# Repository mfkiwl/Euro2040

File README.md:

# Euro2040
 
### An RP2040 based development board designed for use in Eurorack modules

The key aims of this project are to create a board which can be used to create a Eurorack module (or standalone synthesiser) with no need for extra buffering or active circuitry.  
The board will contain internal buffering, amplification, and protection, to allow the GPIO pins to be used with up to 12V signals, allowing users to connect the pins directly to jacks to interface with other Eurorack compliant modules.

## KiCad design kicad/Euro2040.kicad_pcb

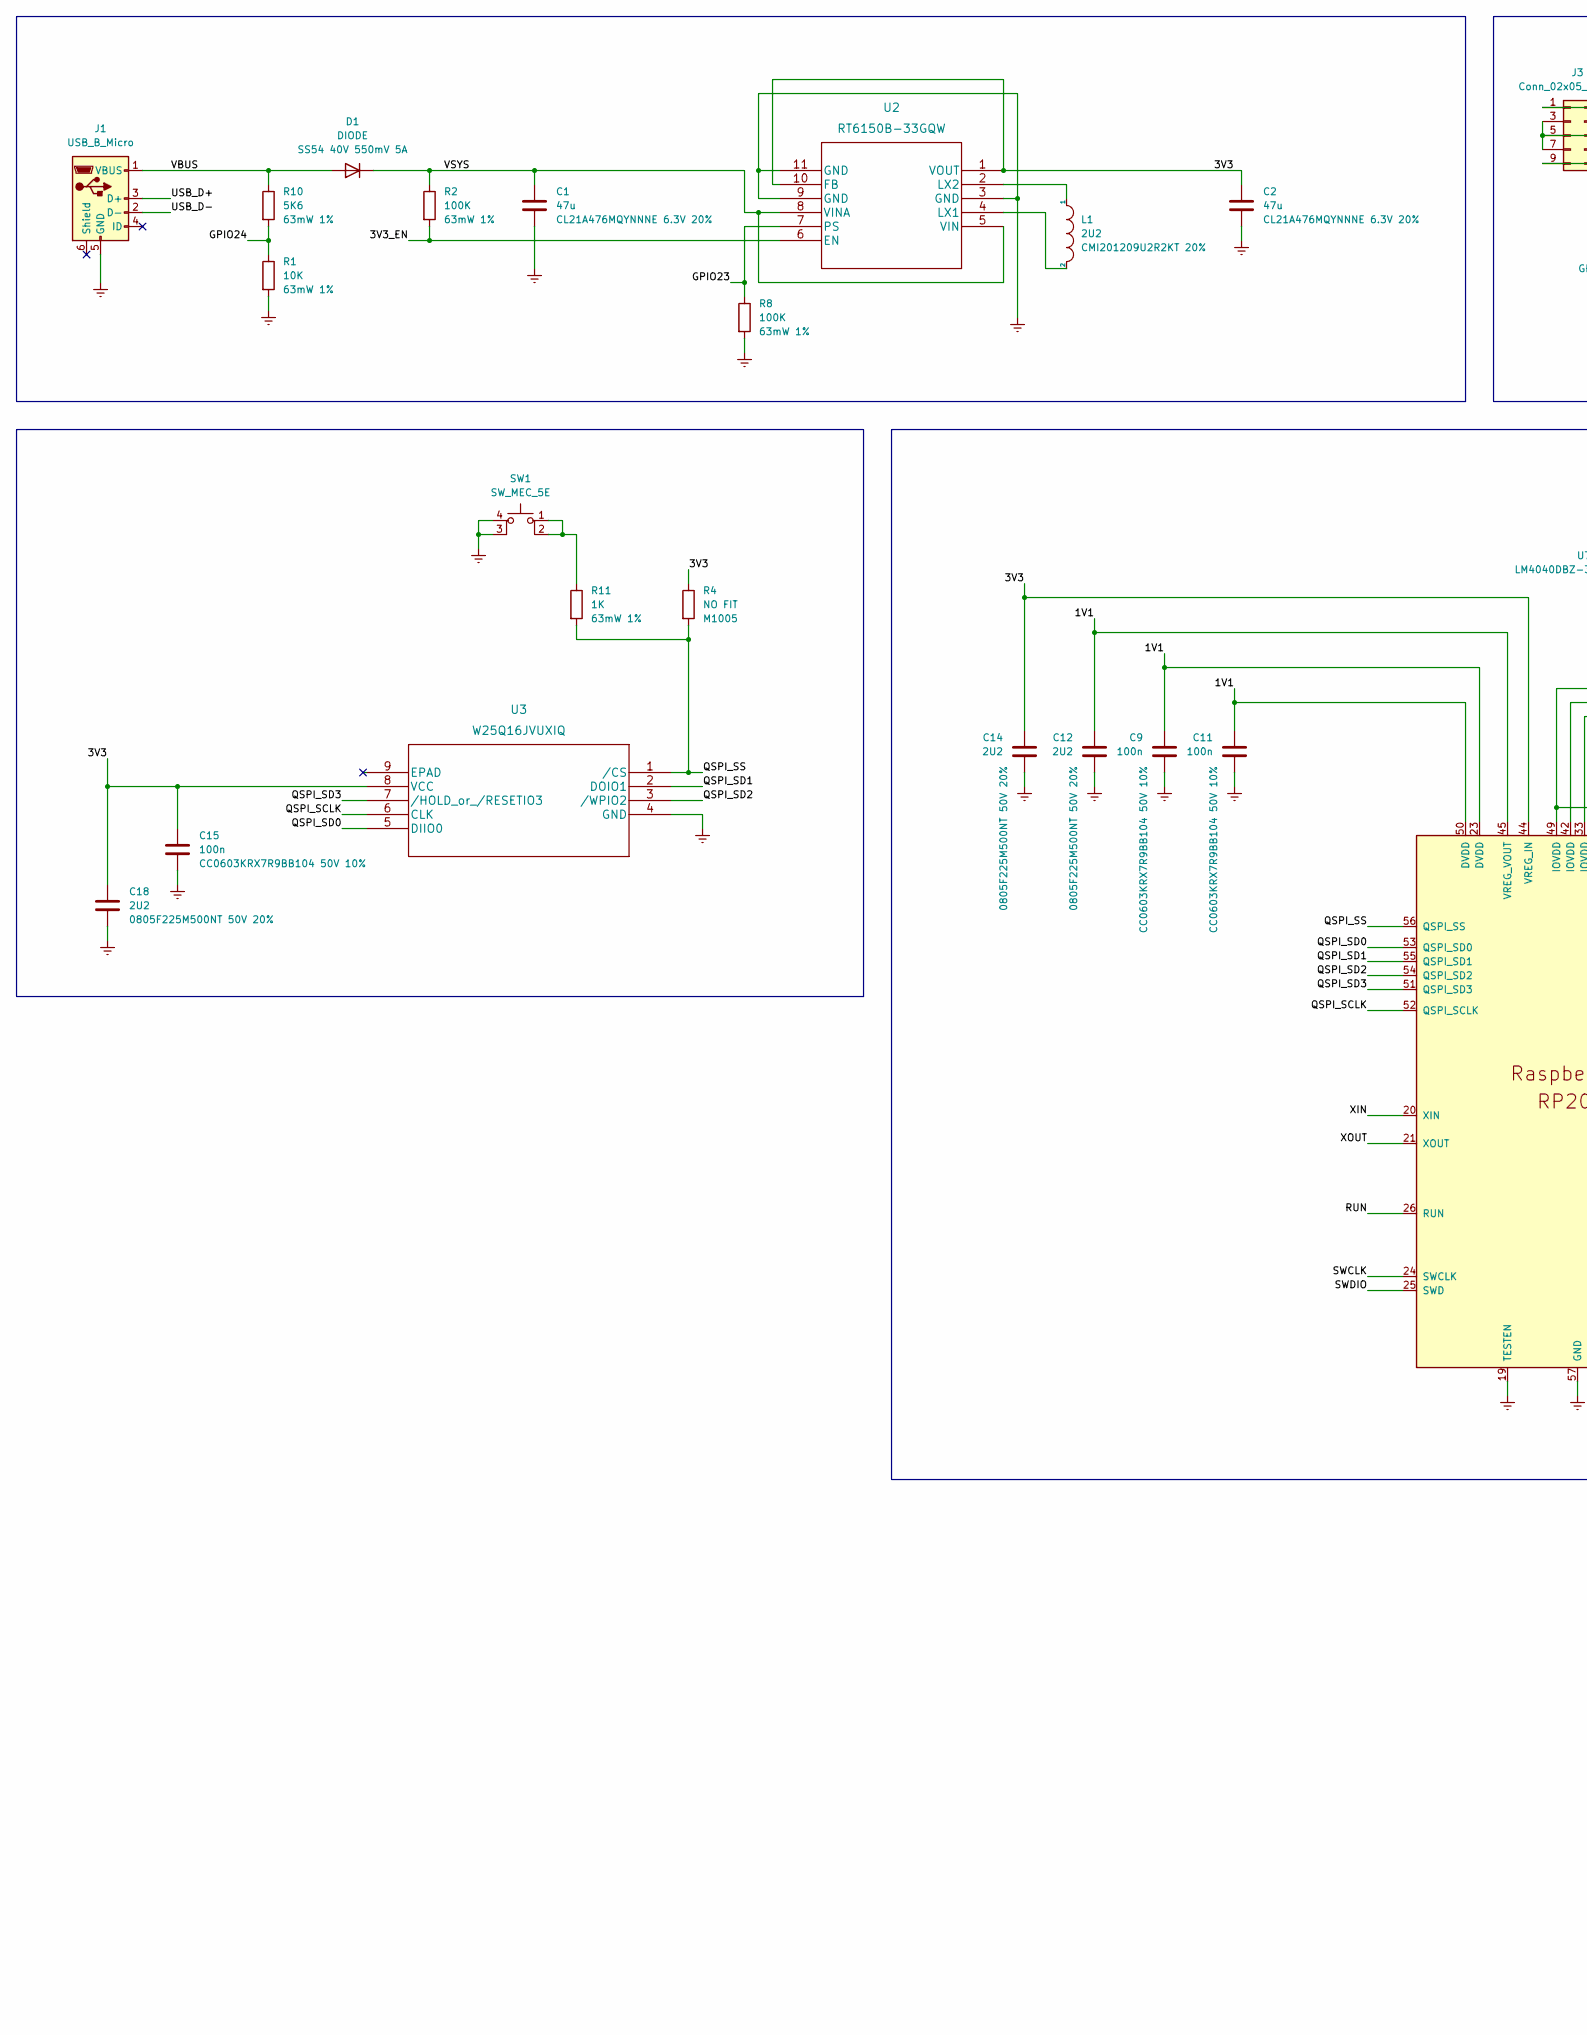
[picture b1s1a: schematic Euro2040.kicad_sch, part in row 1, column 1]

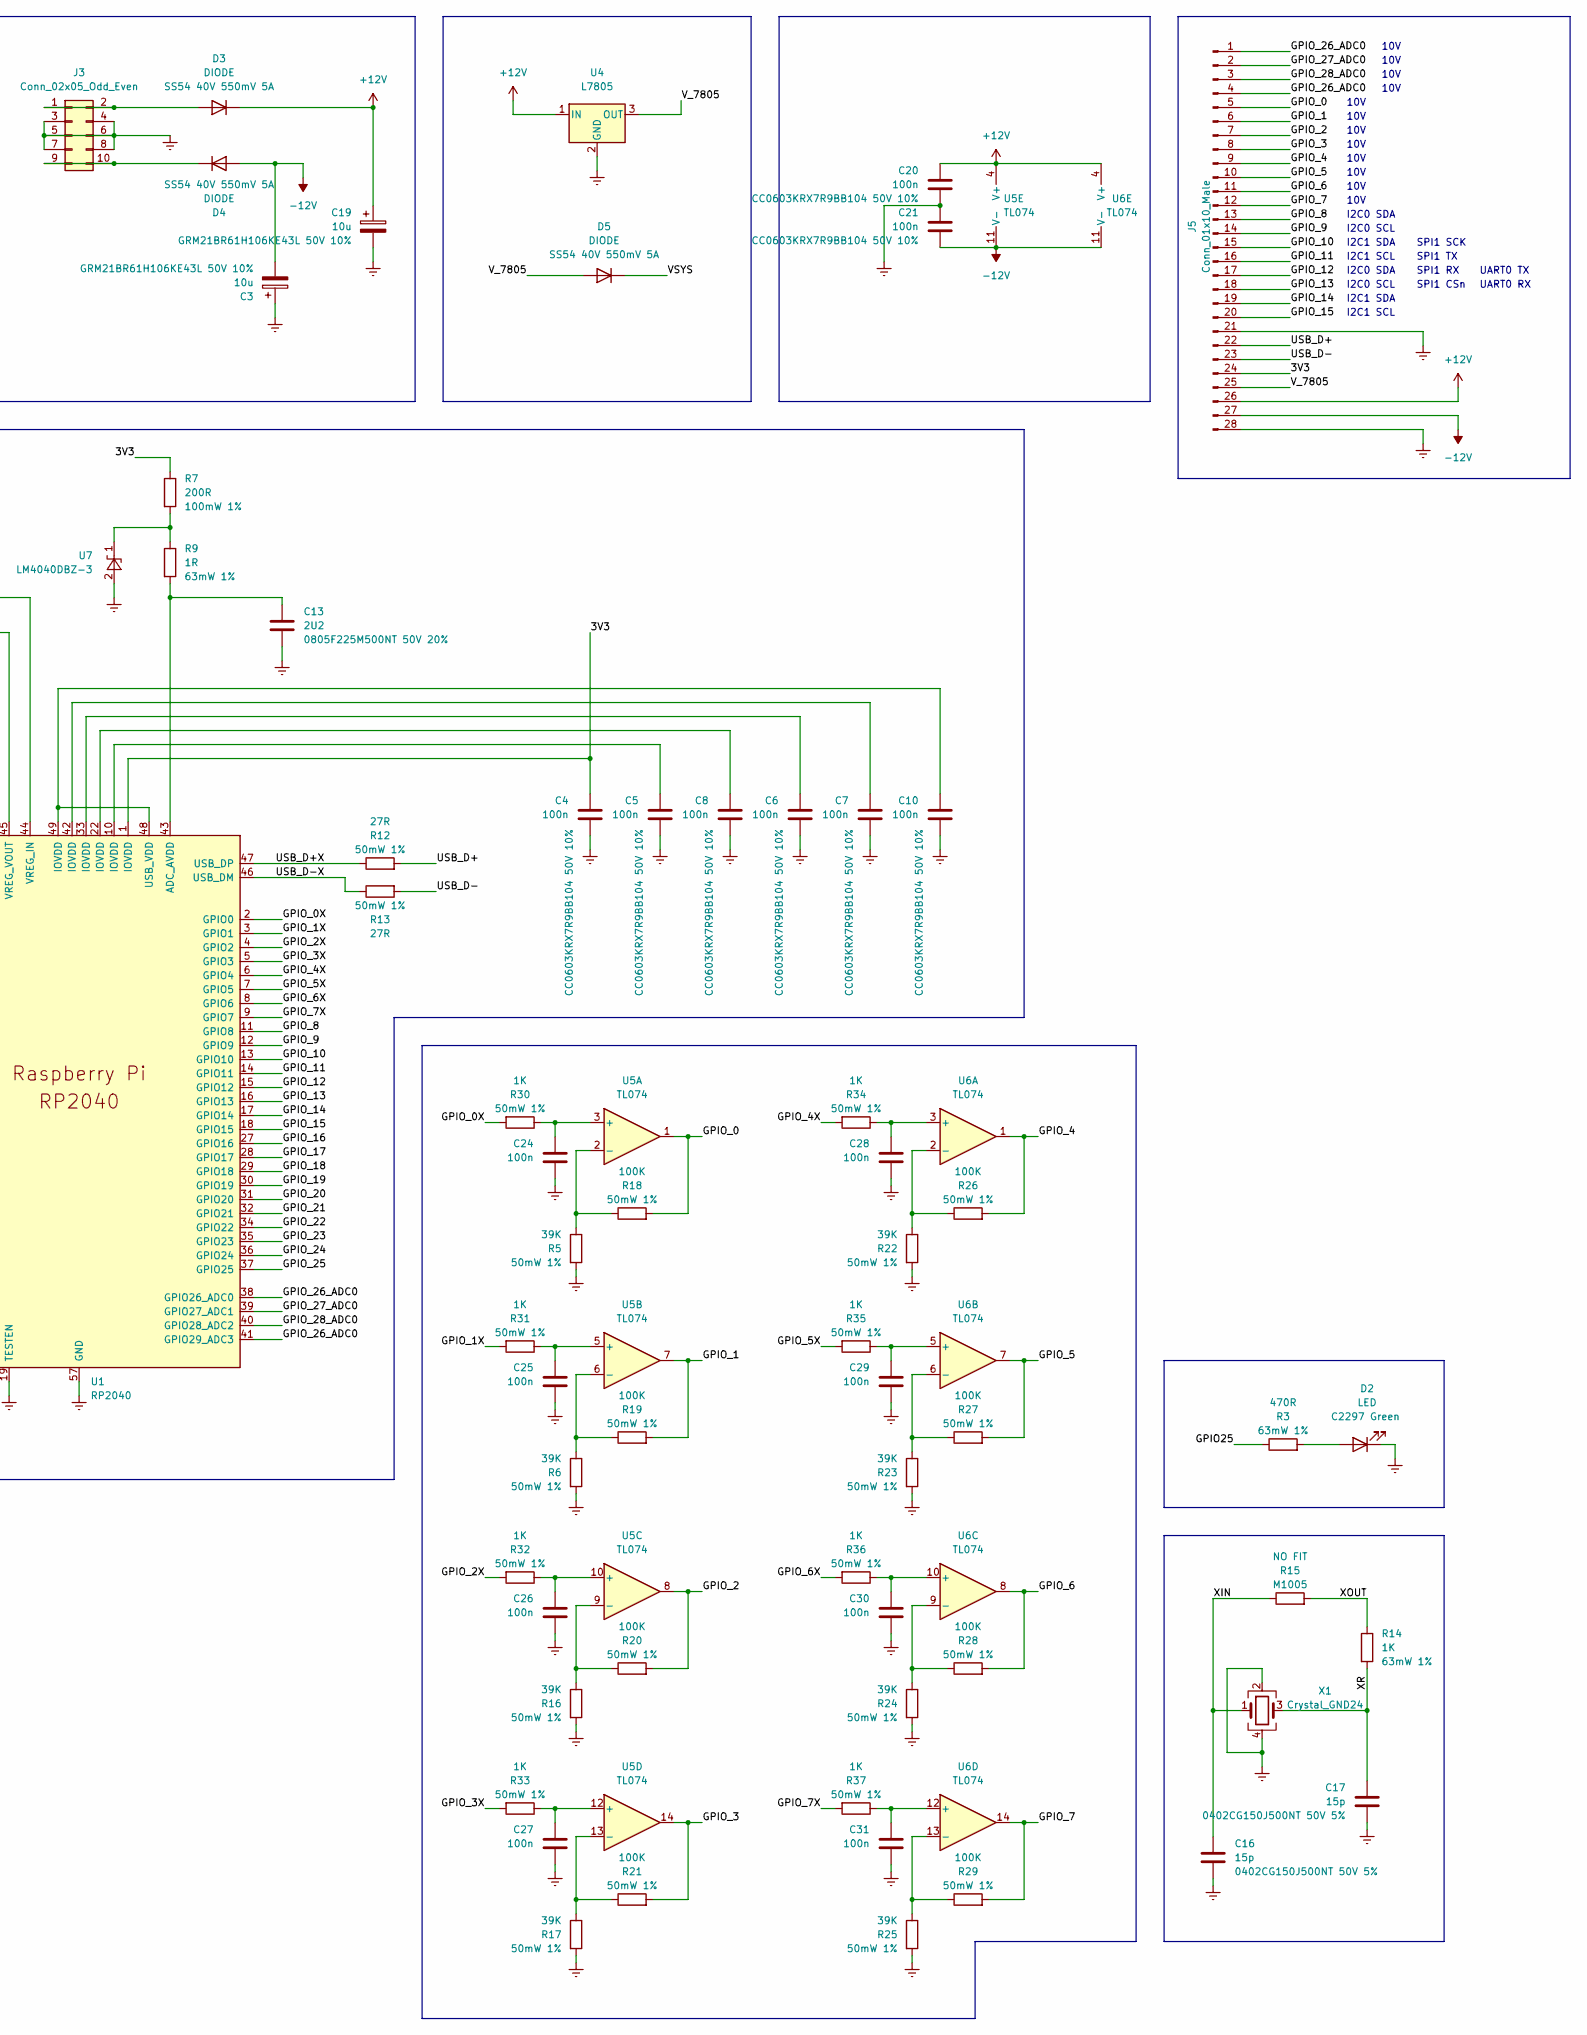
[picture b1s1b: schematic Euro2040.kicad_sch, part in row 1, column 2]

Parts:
C1, C2: 47u; C_0402_1005Metric
C3, C19: 10u; C_0805_2012Metric
C4, C5, C6, C7, C8, C9, C10, C11, C15, C20, C21, C24, C25, C26, C27, C28, C29, C30, C31: 100n; C_0402_1005Metric
C12, C13, C14, C18: 2U2; C_0402_1005Metric
C16, C17: 15p; C_0402_1005Metric
D1, D3, D4, D5: DIODE; D_0805_2012Metric
D2: LED; LED_0402_1005Metric
J1: USB_B_Micro; USB_Micro-B_Amphenol_10103594-0001LF_Horizontal
J3: Conn_02x05_Odd_Even; Eurorack Power Header Unlabeled
J5: Conn_01x10_Male; PinHeader_1x28_P2.00mm_Horizontal
L1: 2U2; L_0402_1005Metric
R1: 10K; R_0402_1005Metric
R2, R8, R18, R19, R20, R21, R26, R27, R28, R29: 100K; R_0402_1005Metric
R3: 470R; R_0402_1005Metric
R4, R15: NO FIT; R_0402_1005Metric
R5, R6, R16, R17, R22, R23, R24, R25: 39K; R_0402_1005Metric
R7: 200R; R_0402_1005Metric
R9: 1R; R_0402_1005Metric
R10: 5K6; R_0402_1005Metric
R11, R14, R30, R31, R32, R33, R34, R35, R36, R37: 1K; R_0402_1005Metric
R12, R13: 27R; R_0402_1005Metric
SW1: SW_MEC_5E; SW_SPST_PTS810
U1: RP2040; QFN40P700X700X90-57N
U2: RT6150B-33GQW
U3: W25Q16JVUXIQ
U4: L7805; SOT-89-3
U5, U6: TL074; SOIC-14_3.9x8.7mm_P1.27mm
U7: LM4040DBZ-3; SOT-23
X1: Crystal_GND24; Crystal_SMD_3225-4Pin_3.2x2.5mm

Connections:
+12V: C19.1, C20.1, D3.2 (K), J5.26, U4.1 (IN), U5.4 (V+), U6.4 (V+)
-12V: C3.2, C21.2, D4.1 (A), J5.27, U5.11 (V-), U6.11 (V-)
/1V1: C9.1, C11.1, C12.1, U1.23 (DVDD), U1.45 (VREG_VOUT), U1.50 (DVDD)
/3V3: C2.1, C4.1, C14.1, C15.1, C18.1, J5.24, R4.1, R7.1, U1.1 (IOVDD), U1.44 (VREG_IN), U2.1 (VOUT), U2.10 (FB), U3.8 (VCC)
/3V3_EN: R2.2, U2.6 (EN)
/GPIO23: R8.1, U2.7 (PS)
/GPIO24: R1.1, R10.2
/GPIO25: R3.1
/GPIO_0: J5.5, R18.2, U5.1
/GPIO_0X: R30.2, U1.2 (GPIO0)
/GPIO_1: J5.6, R19.2, U5.7
/GPIO_1X: R31.2, U1.3 (GPIO1)
/GPIO_2: J5.7, R20.2, U5.8
/GPIO_2X: R32.2, U1.4 (GPIO2)
/GPIO_3: J5.8, R21.2, U5.14
/GPIO_3X: R33.2, U1.5 (GPIO3)
/GPIO_4: J5.9, R26.2, U6.1
/GPIO_4X: R34.2, U1.6 (GPIO4)
/GPIO_5: J5.10, R27.2, U6.7
/GPIO_5X: R35.2, U1.7 (GPIO5)
/GPIO_6: J5.11, R28.2, U6.8
/GPIO_6X: R36.2, U1.8 (GPIO6)
/GPIO_7: J5.12, R29.2, U6.14
/GPIO_7X: R37.2, U1.9 (GPIO7)
/GPIO_8: J5.13, U1.11 (GPIO8)
/GPIO_9: J5.14, U1.12 (GPIO9)
/GPIO_10: J5.15, U1.13 (GPIO10)
/GPIO_11: J5.16, U1.14 (GPIO11)
/GPIO_12: J5.17, U1.15 (GPIO12)
/GPIO_13: J5.18, U1.16 (GPIO13)
/GPIO_14: J5.19, U1.17 (GPIO14)
/GPIO_15: J5.20, U1.18 (GPIO15)
/GPIO_16: U1.27 (GPIO16)
/GPIO_17: U1.28 (GPIO17)
/GPIO_18: U1.29 (GPIO18)
/GPIO_19: U1.30 (GPIO19)
/GPIO_20: U1.31 (GPIO20)
/GPIO_21: U1.32 (GPIO21)
/GPIO_22: U1.34 (GPIO22)
/GPIO_23: U1.35 (GPIO23)
/GPIO_24: U1.36 (GPIO24)
/GPIO_25: U1.37 (GPIO25)
/GPIO_26_ADC0: J5.1, J5.4, U1.38 (GPIO26_ADC0), U1.41 (GPIO29_ADC3)
/GPIO_27_ADC0: J5.2, U1.39 (GPIO27_ADC1)
/GPIO_28_ADC0: J5.3, U1.40 (GPIO28_ADC2)
/QSPI_SCLK: U1.52 (QSPI_SCLK), U3.6 (CLK)
/QSPI_SD0: U1.53 (QSPI_SD0), U3.5 (DIIO0)
/QSPI_SD1: U1.55 (QSPI_SD1), U3.2 (DOIO1)
/QSPI_SD2: U1.54 (QSPI_SD2), U3.3 (/WPIO2)
/QSPI_SD3: U1.51 (QSPI_SD3), U3.7 (/HOLD_or_/RESETIO3)
/QSPI_SS: R4.2, R11.2, U1.56 (QSPI_SS), U3.1 (/CS)
/RUN: U1.26 (RUN)
/SWCLK: U1.24 (SWCLK)
/SWDIO: U1.25 (SWD)
/USB_D+: J1.3 (D+), J5.22, R12.2
/USB_D+X: R12.1, U1.47 (USB_DP)
/USB_D-: J1.2 (D-), J5.23, R13.2
/USB_D-X: R13.1, U1.46 (USB_DM)
/VBUS: D1.1 (A), J1.1 (VBUS), R10.1
/VSYS: C1.1, D1.2 (K), D5.2 (K), R2.1, U2.5 (VIN), U2.8 (VINA)
/V_7805: D5.1 (A), J5.25, U4.3 (OUT)
/XIN: C16.1, R15.1, U1.20 (XIN), X1.1
/XOUT: R14.1, R15.2, U1.21 (XOUT)
/XR: C17.1, R14.2, X1.3
Earth: C1.2, C2.2, C3.1, C4.2, C5.2, C6.2, C7.2, C8.2, C9.2, C10.2, C11.2, C12.2, C13.2, C14.2, C15.2, C16.2, C17.2, C18.2, C19.2, C20.2, C21.1, C24.2, C25.2, C26.2, C27.2, C28.2, C29.2, C30.2, C31.2, D2.1 (K), J1.5 (GND), J3.3, J3.4, J3.5, J3.6, J3.7, J3.8, J5.21, J5.28, R1.2, R5.2, R6.2, R8.2, R16.2, R17.2, R22.2, R23.2, R24.2, R25.2, SW1.3 (K), SW1.4 (A), U1.19 (TESTEN), U1.57 (GND), U2.3 (GND), U2.9 (GND), U2.11 (GND), U3.4 (GND), U4.2 (GND), U7.2 (A), X1.2, X1.4
unnamed: C5.1, U1.10 (IOVDD)
unnamed: C6.1, U1.33 (IOVDD)
unnamed: C7.1, U1.42 (IOVDD)
unnamed: C8.1, U1.22 (IOVDD)
unnamed: C10.1, U1.48 (USB_VDD), U1.49 (IOVDD)
unnamed: C13.1, R9.2, U1.43 (ADC_AVDD)
unnamed: D2.2 (A), R3.2
unnamed: D3.1 (A), J3.1, J3.2
unnamed: D4.2 (K), J3.9, J3.10
unnamed: L1.1, U2.2 (LX2)
unnamed: L1.2, U2.4 (LX1)
unnamed: R7.2, R9.1, U7.1 (K)
unnamed: R11.1, SW1.1, SW1.2
unnamed: R16.1, R20.1, U5.9 (-)
unnamed: R17.1, R21.1, U5.13 (-)
unnamed: R5.1, R18.1, U5.2 (-)
unnamed: R6.1, R19.1, U5.6 (-)
unnamed: R22.1, R26.1, U6.2 (-)
unnamed: R23.1, R27.1, U6.6 (-)
unnamed: R24.1, R28.1, U6.9 (-)
unnamed: R25.1, R29.1, U6.13 (-)
unnamed: C24.1, R30.1, U5.3 (+)
unnamed: C25.1, R31.1, U5.5 (+)
unnamed: C26.1, R32.1, U5.10 (+)
unnamed: C27.1, R33.1, U5.12 (+)
unnamed: C28.1, R34.1, U6.3 (+)
unnamed: C29.1, R35.1, U6.5 (+)
unnamed: C30.1, R36.1, U6.10 (+)
unnamed: C31.1, R37.1, U6.12 (+)

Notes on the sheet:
10V
SPI1 RX
I2C0 SDA
I2C1 SDA
I2C1 SCL
UART0 RX
SPI1 TX
SPI1 CSn
UART0 TX
I2C0 SCL
SPI1 SCK

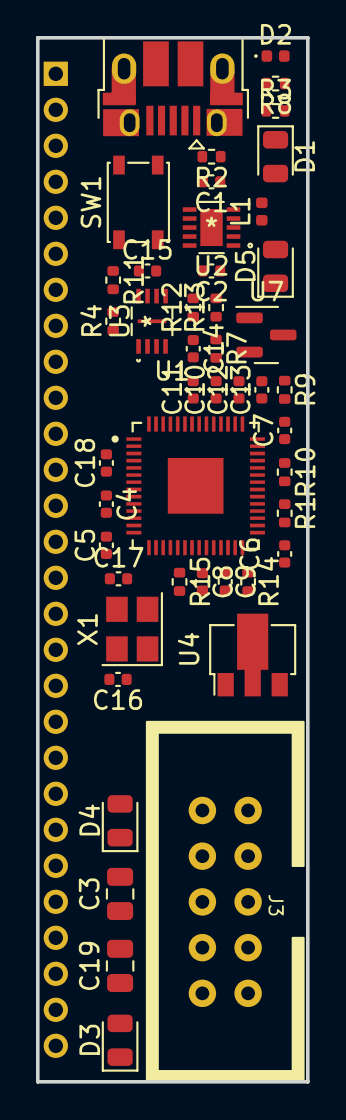
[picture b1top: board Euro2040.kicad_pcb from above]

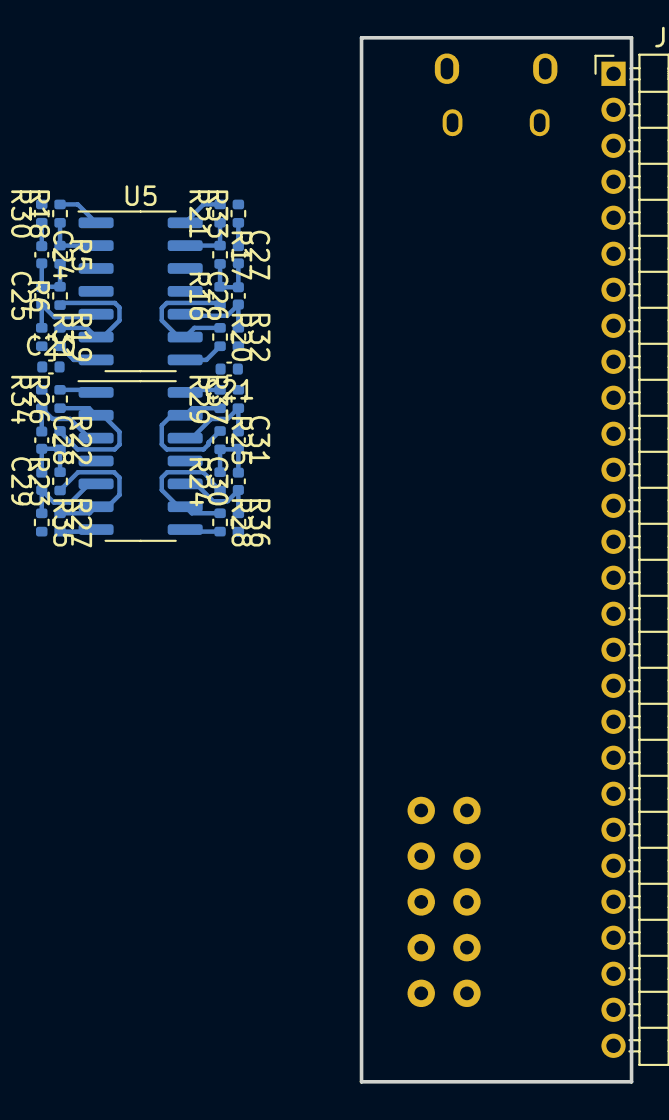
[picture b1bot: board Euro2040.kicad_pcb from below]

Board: 2 copper layers, 15.0 x 58.0 mm, 84 parts (37 on the bottom side), 80 nets.

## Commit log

2022-07-30 create kicad folder
2022-07-31 save
2022-08-01 more pins, output RC filter, pcb layout

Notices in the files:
parts and their libraries:
Copyright 2021 Accelerated Designs. All rights reserved.
